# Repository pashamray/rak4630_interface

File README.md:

# RAK4630 Interface

An open-source hardware breakout / interface board for the **RAK4630** LoRa module (Nordic nRF52840 + Semtech SX1262), designed in KiCad 9.

## Gallery

## Overview

This board provides a minimal interface around the RAK4630 module, exposing its programming and I/O lines on a header and powering it from a USB-C port. It is intended as a development and flashing carrier for the RAK4630.

## Features

- **RAK4630 module** footprint (nRF52840 MCU + SX1262 LoRa radio)
- **USB-C 2.0 receptacle** for power and data
- **TPD2EUSB30** USB ESD protection
- **TLV62569DBV** step-down DC/DC converter for the 3.3 V rail
- **Reset push button**
- **Solder jumper** for power-rail / option configuration
- **8-pin breakout header** for GPIO / SWD / UART access
- **Test points** for key signals

## Repository layout

```
hardware/
├── kicad/      KiCad 9 project (schematic, PCB, project files)
├── gerber/     Manufacturing outputs (Gerbers + drill files)
└── libs/       Project-specific symbol/footprint/3D libraries (RAK4630)
```

## Manufacturing

Ready-to-fab Gerber and Excellon drill files are provided in `hardware/gerber/`. They follow the standard KiCad naming convention and can be uploaded as-is to most PCB fabrication houses.

## Opening the design

1. Install [KiCad 9](https://www.kicad.org/) or newer.
2. Open `hardware/kicad/rak4630_interface.kicad_pro`.

The RAK4630 symbol, footprint and 3D model are bundled under `hardware/libs/RAK4630/` and are referenced via the project library table — no global library setup is required.

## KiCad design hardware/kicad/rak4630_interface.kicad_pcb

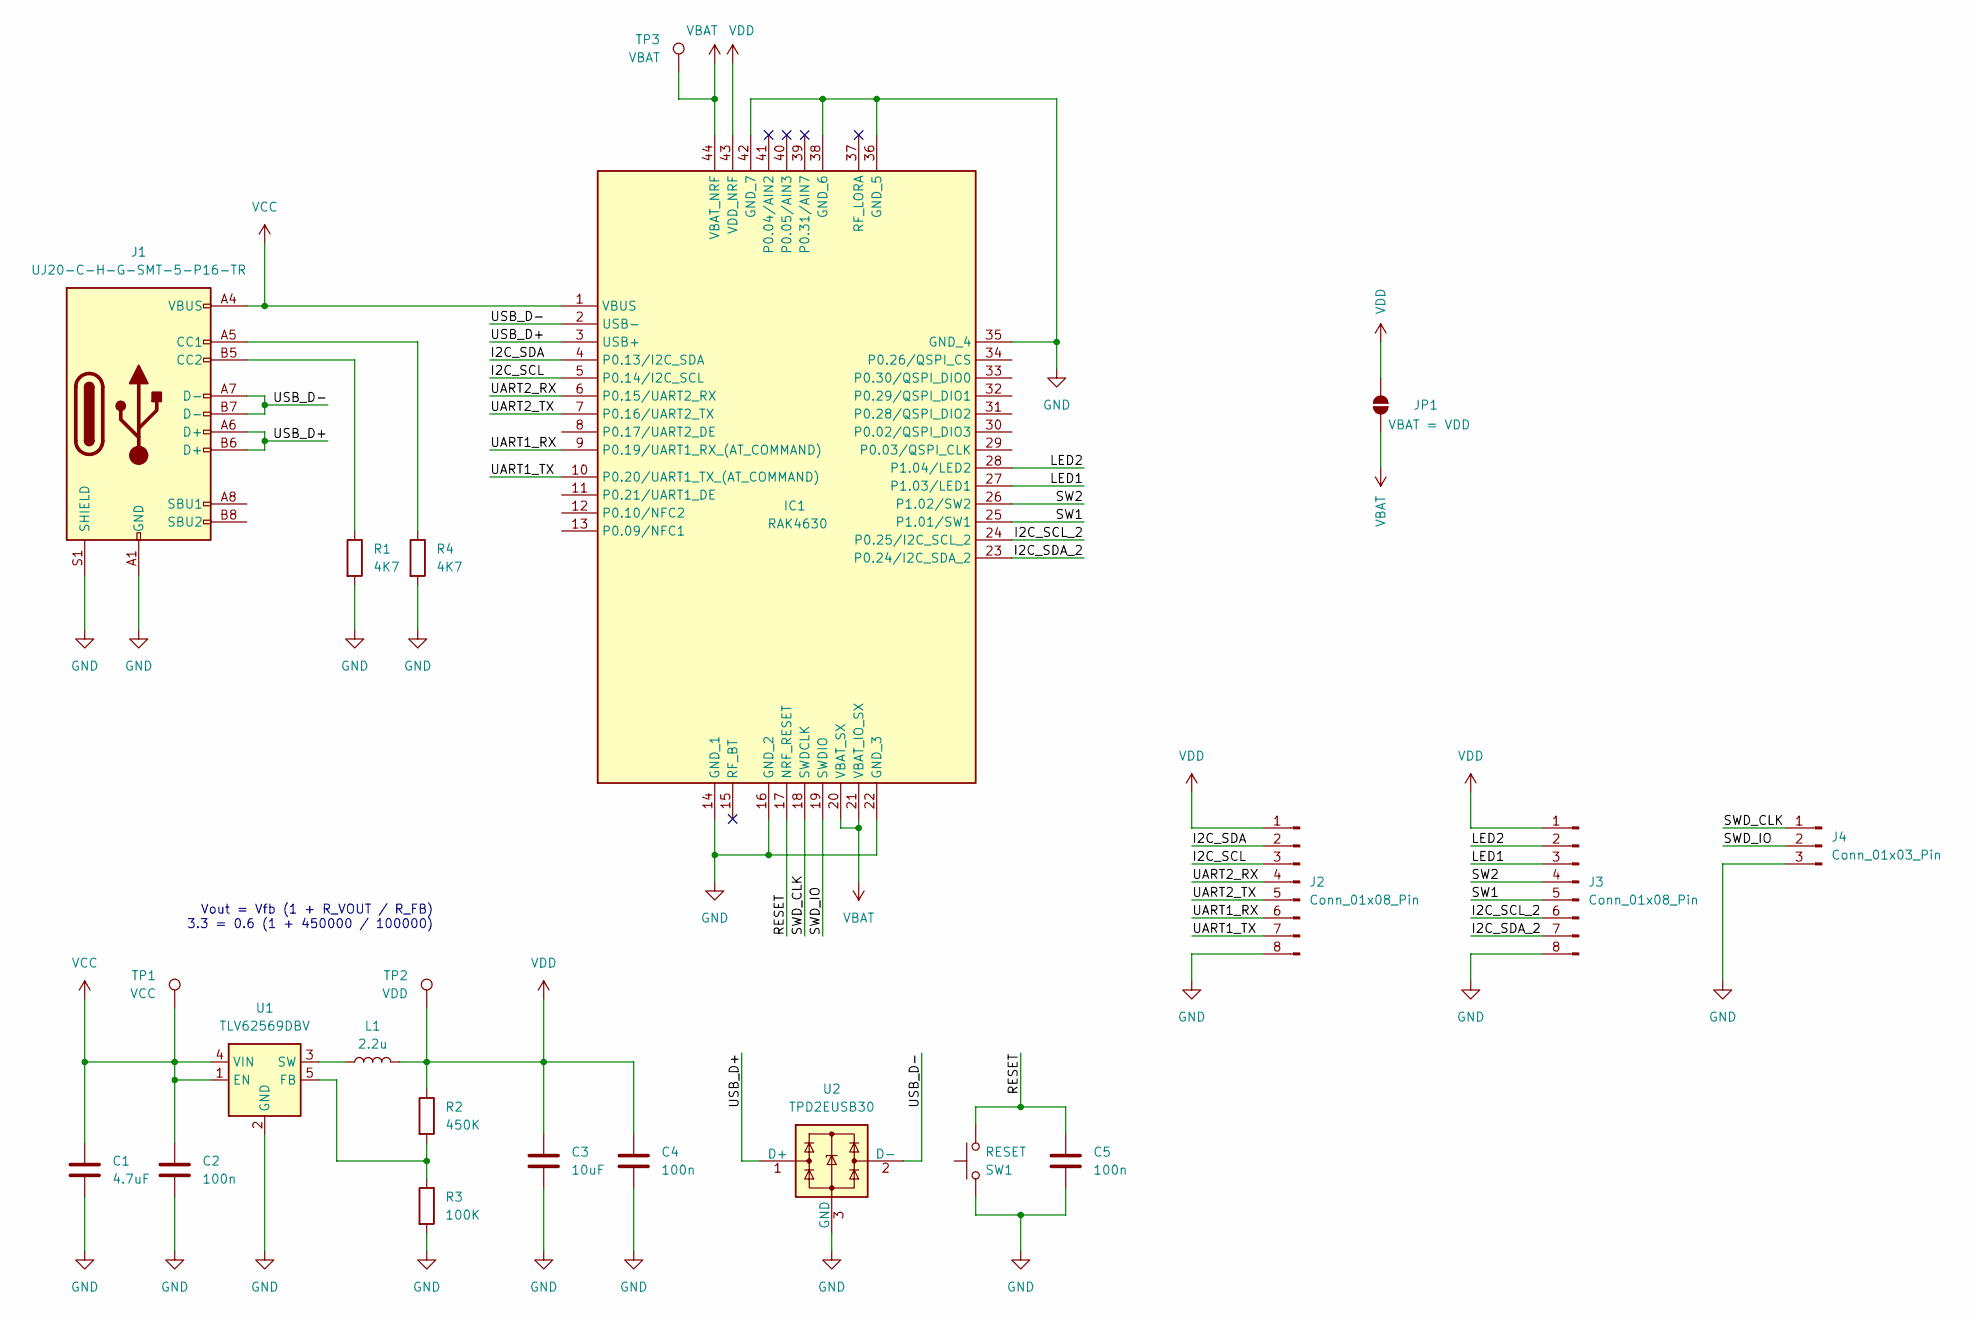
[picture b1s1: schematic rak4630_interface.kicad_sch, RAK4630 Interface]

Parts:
C1: 4.7uF; C_0805_2012Metric
C2, C4, C5: 100n; C_0603_1608Metric
C3: 10uF; C_0805_2012Metric
IC1: RAK4630; Manufacturer_Part_Number RAK4630
J1: UJ20-C-H-G-SMT-5-P16-TR; USB_C_Receptacle_GCT_USB4110
J2, J3: Conn_01x08_Pin; PinSocket_1x08_P2.54mm_Vertical
J4: Conn_01x03_Pin; PinSocket_1x03_P2.54mm_Vertical
JP1: VBAT = VDD; SolderJumper-2_P1.3mm_Open_RoundedPad1.0x1.5mm
L1: 2.2u; L_Wurth_WE-LQSH-4020
R1, R4: 4K7; R_0603_1608Metric
R2: 450K; R_0603_1608Metric
R3: 100K; R_0603_1608Metric
SW1: RESET; SW_SPST_B3U-3000P-B
TP1: VCC; TestPoint_Pad_D1.0mm
TP2: VDD; TestPoint_Pad_D1.0mm
TP3: VBAT; TestPoint_Pad_D1.0mm
U1: TLV62569DBV; SOT-23-5
U2: TPD2EUSB30; Texas_DRT-3

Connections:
/I2C_SCL: IC1.5 (P0.14/I2C_SCL), J2.3
/I2C_SCL_2: IC1.24 (P0.25/I2C_SCL_2), J3.6
/I2C_SDA: IC1.4 (P0.13/I2C_SDA), J2.2
/I2C_SDA_2: IC1.23 (P0.24/I2C_SDA_2), J3.7
/LED1: IC1.27 (P1.03/LED1), J3.3
/LED2: IC1.28 (P1.04/LED2), J3.2
/RESET: C5.1, IC1.17 (NRF_RESET), SW1.1
/SW1: IC1.25 (P1.01/SW1), J3.5
/SW2: IC1.26 (P1.02/SW2), J3.4
/SWD_CLK: IC1.18 (SWDCLK), J4.1
/SWD_IO: IC1.19 (SWDIO), J4.2
/UART1_RX: IC1.9 (P0.19/UART1_RX_(AT_COMMAND)), J2.6
/UART1_TX: IC1.10 (P0.20/UART1_TX_(AT_COMMAND)), J2.7
/UART2_RX: IC1.6 (P0.15/UART2_RX), J2.4
/UART2_TX: IC1.7 (P0.16/UART2_TX), J2.5
/USB_D+: IC1.3 (USB+), J1.A6 (D+), J1.B6 (D+), U2.1 (D+)
/USB_D-: IC1.2 (USB-), J1.A7 (D-), J1.B7 (D-), U2.2 (D-)
GND: C1.2, C2.2, C3.2, C4.2, C5.2, IC1.14 (GND_1), IC1.16 (GND_2), IC1.22 (GND_3), IC1.35 (GND_4), IC1.36 (GND_5), IC1.38 (GND_6), IC1.42 (GND_7), J1.A1 (GND), J1.A12 (GND), J1.B1 (GND), J1.B12 (GND), J1.S1 (SHIELD), J2.8, J3.8, J4.3, R1.2, R3.2, R4.2, SW1.2, U1.2 (GND), U2.3 (GND)
unnamed: J1.A5 (CC1), R4.1
unnamed: J1.B5 (CC2), R1.1
unnamed: R2.2, R3.1, U1.5 (FB)
unnamed: L1.2, U1.3 (SW)
VBAT: IC1.20 (VBAT_SX), IC1.21 (VBAT_IO_SX), IC1.44 (VBAT_NRF), JP1.2 (B), TP3.1
VCC: C1.1, C2.1, IC1.1 (VBUS), J1.A4 (VBUS), J1.A9 (VBUS), J1.B4 (VBUS), J1.B9 (VBUS), TP1.1, U1.1 (EN), U1.4 (VIN)
VDD: C3.1, C4.1, IC1.43 (VDD_NRF), J2.1, J3.1, JP1.1 (A), L1.1, R2.1, TP2.1

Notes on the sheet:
Vout = Vfb (1 + R_VOUT / R_FB) 3.3 = 0.6 (1 + 450000 / 100000)

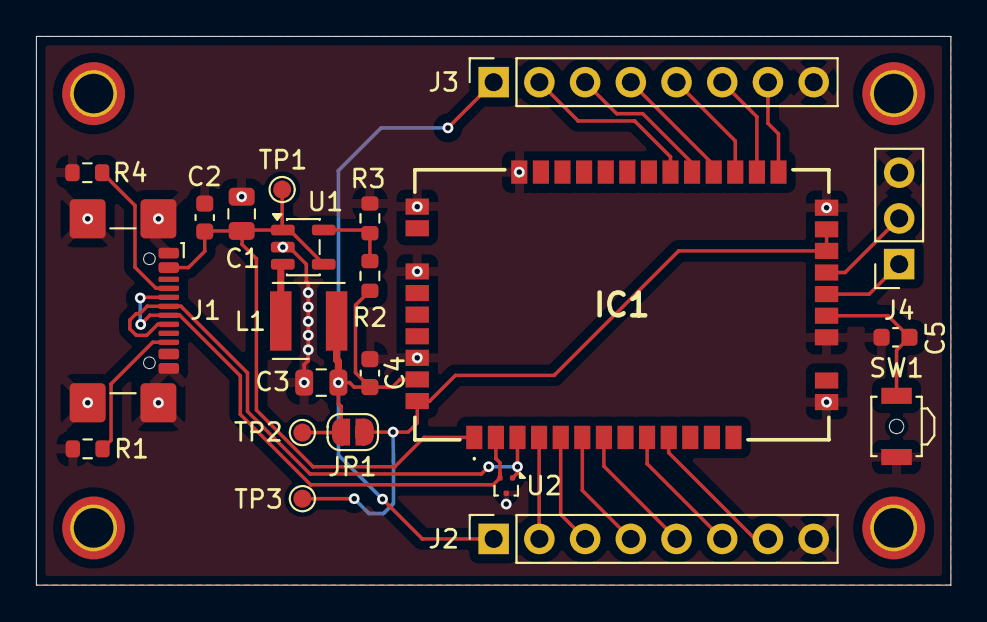
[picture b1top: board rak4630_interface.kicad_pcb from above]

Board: 2 copper layers, 50.8 x 30.5 mm, 22 parts (0 on the bottom side), 25 nets.

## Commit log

2026-04-10 Remove license section from README
    Removed license section from README.md
2026-04-10 Update README to remove SWD access mention
2026-04-10 update pcb
2026-04-10 Update README to include SWD in breakout header
2026-04-10 update annotations
